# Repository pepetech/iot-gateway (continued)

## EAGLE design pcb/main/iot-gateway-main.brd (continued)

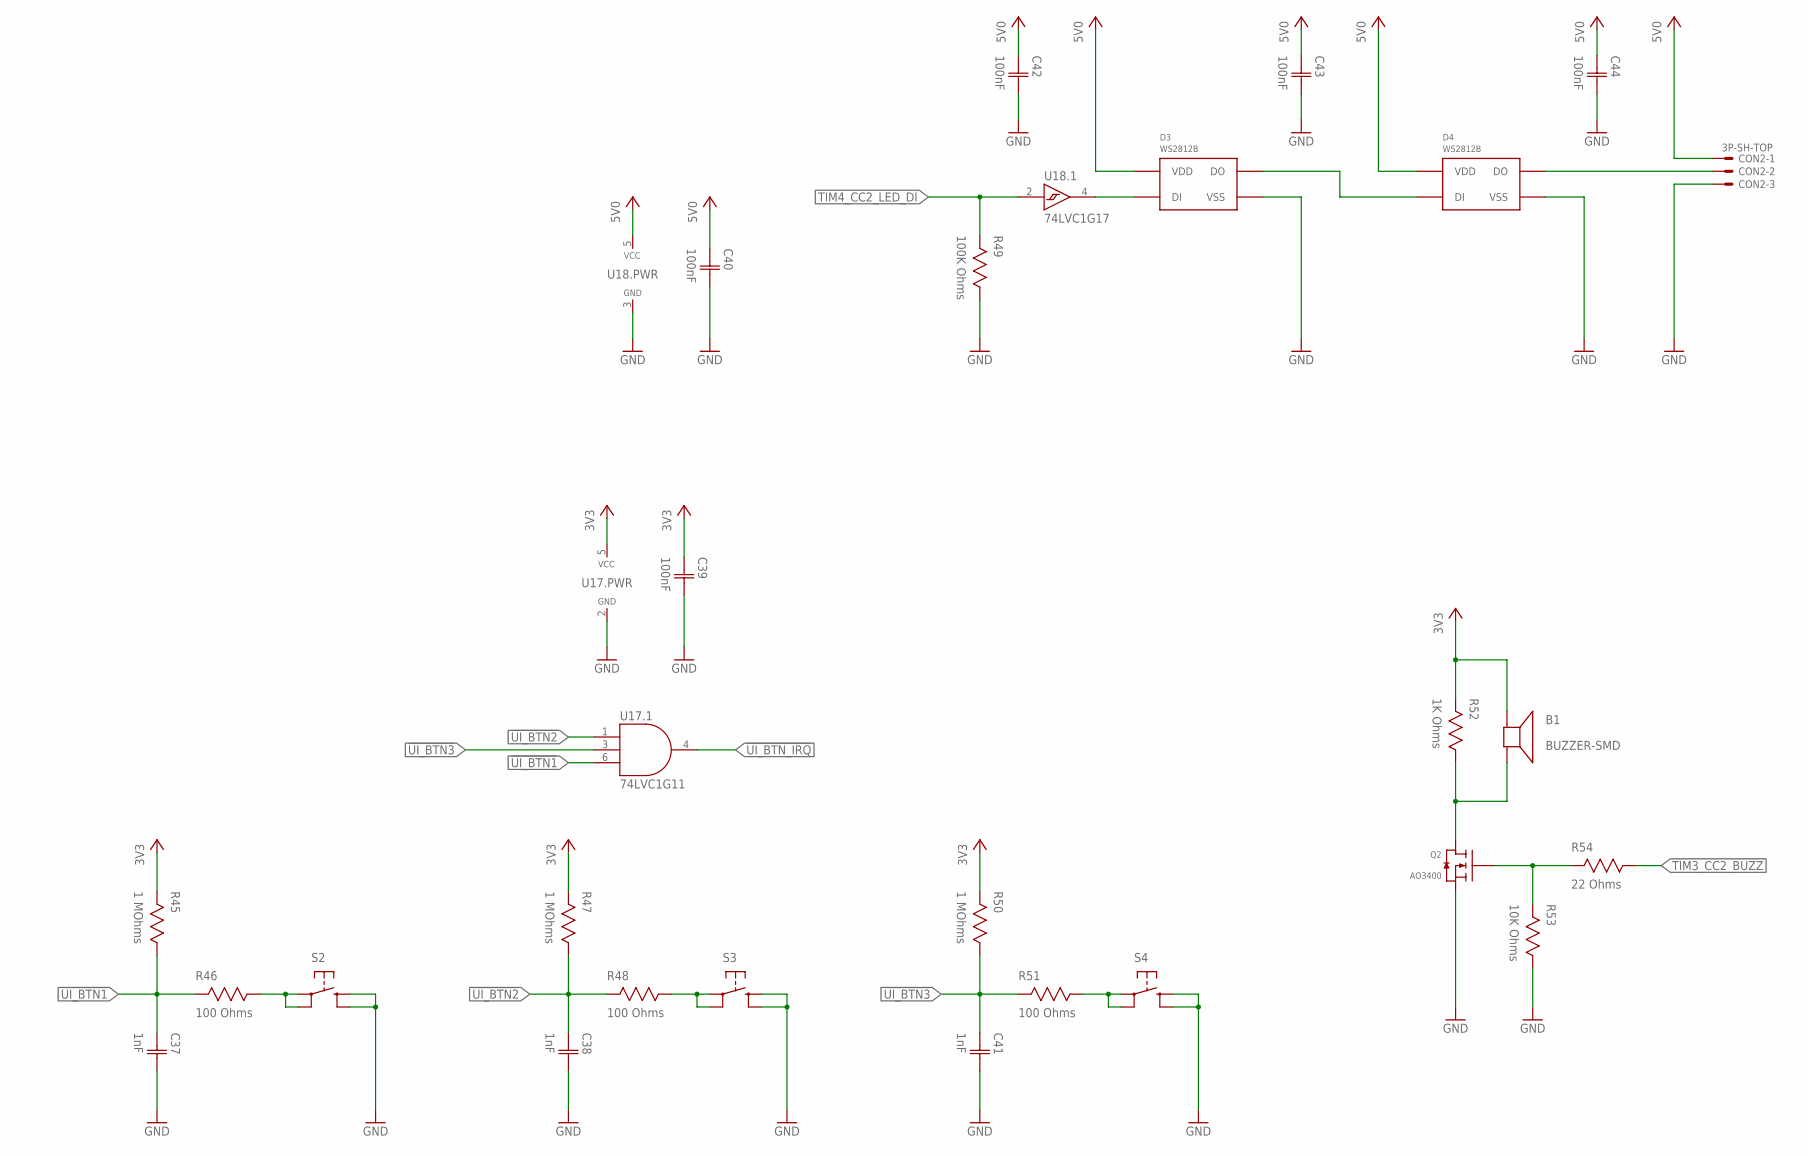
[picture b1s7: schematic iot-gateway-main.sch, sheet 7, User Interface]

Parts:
B1: BUZZER-SMD; SMD
C37, C38, C41: 1nF; CAP0603
C39, C40, C42, C43, C44: 100nF; CAP0603
CON2: 3P-SH-TOP; SH-03-TOP
D3, D4: WS2812B; WS2812B-SMD5050
Q2: AO3400; SOT23
R45, R47, R50: 1 MOhms; RES0603
R46, R48, R51: 100 Ohms; RES0603
R49: 100K Ohms; RES0603
R52: 1K Ohms; RES0603
R53: 10K Ohms; RES0603
R54: 22 Ohms; RES0603
S2, S3, S4: TAC_SWITCHSMD_4.5X4.5; TAC_SW_SMD_4.5X4.5
U17: 74LVC1G11; SC70-6
U18: 74LVC1G17; SC70-5

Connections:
3V3: B1.1 (+), C39.1 (C1), R45.2, R47.2, R50.2, R52.2, U17.5 (VCC); also elsewhere on the board
5V0: C40.1 (C1), C42.1 (C1), C43.1 (C1), C44.1 (C1), CON2.1, D3.1 (VDD), D4.1 (VDD), U18.5 (VCC); also elsewhere on the board
!UI_BTN1: C37.1 (C1), R45.1, R46.2, U17.6 (C); also elsewhere on the board
!UI_BTN2: C38.1 (C1), R47.1, R48.2, U17.1 (A); also elsewhere on the board
!UI_BTN3: C41.1 (C1), R50.1, R51.2, U17.3 (B); also elsewhere on the board
!UI_BTN_IRQ: U17.4 (Y); also elsewhere on the board
BUZZ_DRV: B1.2 (-), Q2.3 (D), R52.1
EXT_LED_DI: CON2.2, D4.2 (DO)
GND: C37.2 (C2), C38.2 (C2), C39.2 (C2), C40.2 (C2), C41.2 (C2), C42.2 (C2), C43.2 (C2), C44.2 (C2), CON2.3, D3.3 (VSS), D4.3 (VSS), Q2.2 (S), R49.1, R53.1, S2.3, S2.4, S3.3, S3.4, S4.3, S4.4, U17.2 (GND), U18.3 (GND); also elsewhere on the board
LED1_DI: D3.4 (DI), U18.4 (Y)
LED2_DI: D3.2 (DO), D4.4 (DI)
unnamed: Q2.1 (G), R53.2, R54.2
unnamed: R46.1, S2.1, S2.2
unnamed: R51.1, S4.1, S4.2
unnamed: R48.1, S3.1, S3.2
TIM3_CC2_BUZZ: R54.1; also elsewhere on the board
TIM4_CC2_LED_DI: R49.2, U18.2 (A); also elsewhere on the board

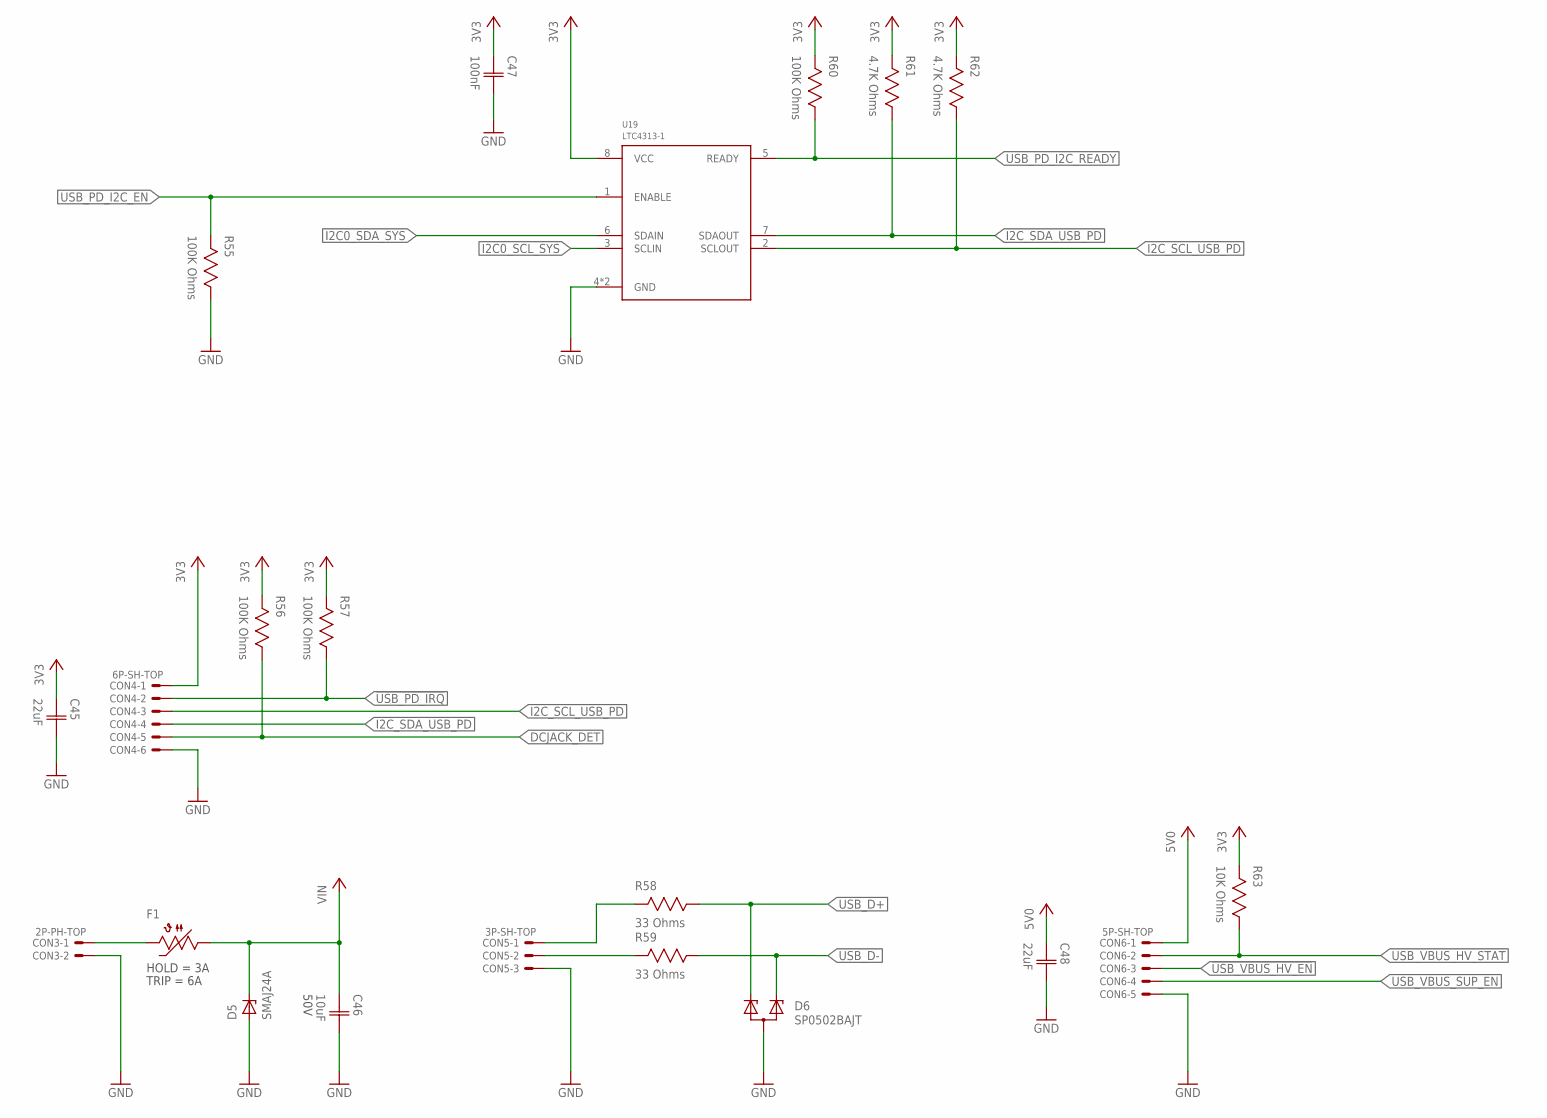
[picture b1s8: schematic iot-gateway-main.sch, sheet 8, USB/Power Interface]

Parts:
C45, C48: 22uF; CAP1206
C46: 10uF; CAP1206; VOLTAGE 50V
C47: 100nF; CAP0603
CON3: 2P-PH-TOP; PH-02-TOP
CON4: 6P-SH-TOP; SH-06-TOP
CON5: 3P-SH-TOP; SH-03-TOP
CON6: 5P-SH-TOP; SH-05-TOP
D5: SMAJ24A; DO214AC
D6: SP0502BAJT; SC70-3
F1: 2.6A Hold; 1206
R55, R56, R57, R60: 100K Ohms; RES0603
R58, R59: 33 Ohms; RES0603
R61, R62: 4.7K Ohms; RES0603
R63: 10K Ohms; RES0603
U19: LTC4313-1; DFN8

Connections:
3V3: C45.1 (C1), C47.1 (C1), CON4.1, R56.2, R57.2, R60.2, R61.2, R62.2, R63.2, U19.8 (VCC); also elsewhere on the board
5V0: C48.1 (C1), CON6.1; also elsewhere on the board
!USB_PD_IRQ: CON4.2, R57.1; also elsewhere on the board
!USB_VBUS_HV_EN: CON6.3; also elsewhere on the board
DCJACK_DET: CON4.5, R56.1; also elsewhere on the board
GND: C45.2 (C2), C46.2 (C2), C47.2 (C2), C48.2 (C2), CON3.2, CON4.6, CON5.3, CON6.5, D5.A, D6.3 (A), R55.1, U19.4 (GND), U19.9 (GND); also elsewhere on the board
I2C0_SCL_SYS: U19.3 (SCLIN); also elsewhere on the board
I2C0_SDA_SYS: U19.6 (SDAIN); also elsewhere on the board
I2C_SCL_USB_PD: CON4.3, R62.1, U19.2 (SCLOUT)
I2C_SDA_USB_PD: CON4.4, R61.1, U19.7 (SDAOUT)
unnamed: CON5.2, R59.2
unnamed: CON5.1, R58.2
USB_D+: D6.1 (C1), R58.1; also elsewhere on the board
USB_D-: D6.2 (C2), R59.1; also elsewhere on the board
USB_PD_I2C_EN: R55.2, U19.1 (ENABLE); also elsewhere on the board
USB_PD_I2C_READY: R60.1, U19.5 (READY); also elsewhere on the board
USB_VBUS_HV_STAT: CON6.2, R63.1; also elsewhere on the board
USB_VBUS_SUP_EN: CON6.4; also elsewhere on the board
VIN: C46.1 (C1), D5.C, F1.1; also elsewhere on the board
VIN_UNFUSED: CON3.1, F1.2

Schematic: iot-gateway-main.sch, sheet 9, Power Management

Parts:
C49, C55, C62, C69, C70, C71, C73, C75, C76: 100nF; CAP0603
C50: 4.7uF; CAP0603; VOLTAGE 35V
C51, C72: 4.7uF; CAP0603
C52, C54: 1uF; CAP0603; VOLTAGE 50V
C53, C59, C60, C61, C64, C65, C74: 470pF; CAP0603
C56: 1uF; CAP0603
C57, C66, C78: 100uF; CAP1206
C58: 10nF; CAP0603
C63: 10pF; CAP0603
C67, C77: 10uF; CAP0603
C68, C79: 22uF; CAP1206
CON7: 2P-PH-TOP; PH-02-TOP
D7: LED1206-REV; 1206_REV
D8: RED; 1206_REV
L3: 470nH; IND3225
L4: 4.7uH; IND0606
L5: 1uH; IND0805
L6: 2.2uH; IND0505
Q3: AO3400; SOT23
Q4: FS8205; SOT23-6
R64: 147K Ohms; RES0603
R65: 21K Ohms; RES0603
R66, R67, R68, R72, R73, R74, R75, R76, R77, R86, R87, R88, R89, R91: 100K Ohms; RES0603
R69: 357K Ohms; RES0603
R70: 61.9K Ohms; RES0603
R71: 41.2K Ohms; RES0603
R78: 1M Ohms; RES0603
R79: 232K Ohms; RES0603
R80: 309K Ohms; RES0603
R81: 71.5K Ohms; RES0603
R82: 510 Ohms; RES0603
R83: 178K Ohms; RES0603
R84: 57.6K Ohms; RES0603
R85: 330 Ohms; RES0603
R90, R95: 2K Ohms; RES0603
R92: 25m Ohms; RES1206
R93: 10m Ohms; RES1206
R94: 100 Ohms; RES0603
R96: 1.5M Ohms; RES0603
R97: 274K Ohms; RES0603
U20: LT8640S; QFN24_CORNER
U21: MIC23159; VQFN20
U22: 74LVC1G04; SC70-5
U23: LTC2942; DFN6
U24: LTC4040; QFN24_ASYM
U25: FS312F-G; SOT23-6

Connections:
3V3: C67.1 (C1), C69.1 (C1), C73.1 (C1), L5.2, R72.2, R73.2, R80.2, R86.2, R87.2, R88.2, R89.2, R91.2, U21.10 (SNS), U22.5 (VCC); also elsewhere on the board
3V3_FB: R80.1, R81.2, U21.11 (FB)
3V3_SS: C64.1 (C1), U21.13 (SS)
3V3_SW: L5.1, U21.4 (SW)
4V2: C55.1 (C1), C57.1 (C1), L3.1, R67.2, R69.2, U21.17 (SNS); also elsewhere on the board
4V2_EN: R66.2, U21.18 (EN); also elsewhere on the board
4V2_FB: R69.1, R70.2, U21.16 (FB)
4V2_PGOOD: R73.1, U21.15 (PG); also elsewhere on the board
4V2_SS: C60.1 (C1), U21.14 (SS)
4V2_SW: L3.2, U21.3 (SW)
4V2_VSENSE: C59.1 (C1), R67.1, R68.2; also elsewhere on the board
5V0: C49.1 (C1), C51.1 (C1), C71.1 (C1), C72.1 (C1), C78.1 (C1), C79.1 (C1), Q3.3 (D), R74.2, R96.2, U21.1 (VIN), U21.6 (VIN), U21.7 (AVIN), U21.9 (EN), U21.20 (AVIN), U24.1 (VSYS), U24.12 (F2), U24.13 (F1), U24.14 (F0), U24.24 (VSYS); also elsewhere on the board
5V0_BACKUP: R85.2, U22.4 (Y)
5V0_FB: R96.1, R97.2, U24.10 (RSTFB), U24.18 (BSTFB)
5V0_GATE: Q3.1 (G), U24.15 (IGATE)
5V0_NBU: Q3.2 (S), R93.1, U24.7 (CLN)
5V0_NBU_ISENSE: C74.1 (C1), U24.3 (CLPROG); also elsewhere on the board
5V0_NBU_NSENS: C63.1 (C1), C66.1 (C1), C68.1 (C1), C70.1 (C1), L4.2, R78.2, R82.2, R83.2, R93.2, U20.1 (BIAS), U24.6 (VIN), U24.16 (OVSNS)
5V0_NBU_NSENS_BST: C62.2 (C2), U20.7 (BST)
5V0_NBU_NSENS_FB: C63.2 (C2), R78.1, R79.2, U20.24 (FB)
5V0_NBU_NSENS_INTVCC: C56.1 (C1), U20.2 (INTVCC), U20.20 (SYNC/MODE)
5V0_NBU_NSENS_PGOOD: R72.1, U20.23 (PG); also elsewhere on the board
5V0_NBU_NSENS_RT: R71.2, U20.18 (RT)
5V0_NBU_NSENS_SS: C58.1 (C1), U20.21 (TR/SS)
5V0_NBU_NSENS_SW: C62.1 (C1), L4.1, U20.8 (SW), U20.9 (SW), U20.10 (SW), U20.11 (SW), U20.12 (SW)
5V0_VSENSE: C61.1 (C1), R74.1, R75.2; also elsewhere on the board
!5V0_BACKUP: R87.1, U22.2 (A), U24.20 (!PFO); also elsewhere on the board
!BAT_CHRG: R89.1, U24.8 (!CHRG); also elsewhere on the board
!BAT_CHRG_EN: R91.1, U24.4 (CHGOFF); also elsewhere on the board
!BAT_FAULT: R88.1, U24.9 (!FAULT); also elsewhere on the board
!FUEL_GAUGE_IRQ: R86.1, U23.5 (!AL!/CC); also elsewhere on the board
BAT_CHRG_PROG: R90.2, U24.2 (PROG)
BAT_OC: Q4.6 (G1), U25.3 (OC)
BAT_OD: Q4.4 (G2), U25.1 (OD)
BAT_PROT_CS: R95.2, U25.2 (CS)
BAT_PROT_VCC: R94.1, U25.5 (VCC)
GBAT: C75.2 (C2), CON7.2, Q4.3 (S2), U25.6 (GND)
GND: C49.2 (C2), C50.2 (C2), C51.2 (C2), C52.2 (C2), C53.2 (C2), C54.2 (C2), C55.2 (C2), C56.2 (C2), C57.2 (C2), C58.2 (C2), C59.2 (C2), C60.2 (C2), C61.2 (C2), C64.2 (C2), C65.2 (C2), C66.2 (C2), C67.2 (C2), C68.2 (C2), C69.2 (C2), C70.2 (C2), C71.2 (C2), C72.2 (C2), C73.2 (C2), C74.2 (C2), C76.2 (C2), C77.2 (C2), C78.2 (C2), C79.2 (C2), D7.C, D8.C, Q4.1 (S1), R65.1, R66.1, R68.1, R70.1, R71.1, R75.1, R77.1, R79.1, R81.1, R84.1, R90.1, R95.1, R97.1, U20.3 (GND), U20.16 (GND), U20.22 (GND), U20.25 (GND), U20.26 (GND), U20.27 (GND), U20.28 (GND), U20.29 (GND), U20.30 (GND), U20.31 (GND), U20.32 (GND), U21.2 (PGND), U21.5 (PGND), U21.8 (AGND), U21.19 (AGND), U21.21 (PGND), U22.3 (GND), U23.2 (GND), U24.5 (BSTOFF), U24.17 (NTC), U24.25 (GND); also elsewhere on the board
I2C0_SCL_SYS: U23.3 (SCL); also elsewhere on the board
I2C0_SDA_SYS: U23.4 (SDA); also elsewhere on the board
unnamed: D7.A, R82.1
unnamed: D8.A, R85.1
PF_THRESH: R83.1, R84.2, U24.19 (PFI)
VBAT: C75.1 (C1), C76.1 (C1), C77.1 (C1), L6.2, R76.2, R92.2, R94.2, U23.1 (VDD/SENSE+), U24.23 (BAT)
VBAT_NSENS: CON7.1, R92.1, U23.6 (VBAT/SENSE-)
VBAT_SW: L6.1, U24.21 (SW), U24.22 (SW)
VBAT_VSENSE: C65.1 (C1), R76.1, R77.2; also elsewhere on the board
VIN: C50.1 (C1), C52.1 (C1), C54.1 (C1), R64.2, U20.5 (VIN), U20.6 (VIN), U20.13 (VIN), U20.14 (VIN), U20.17 (EN/UV); also elsewhere on the board
VIN_VSENSE: C53.1 (C1), R64.1, R65.2; also elsewhere on the board

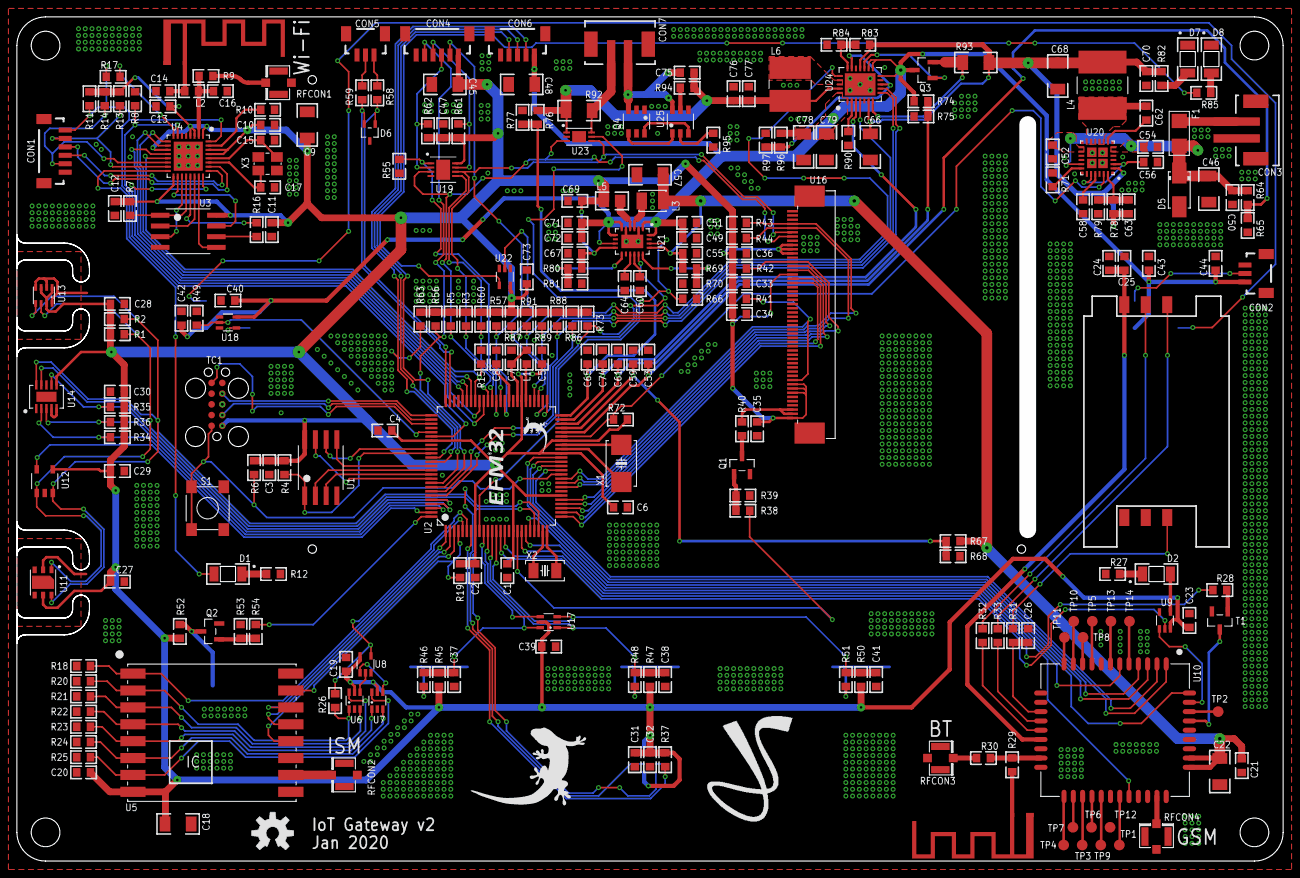
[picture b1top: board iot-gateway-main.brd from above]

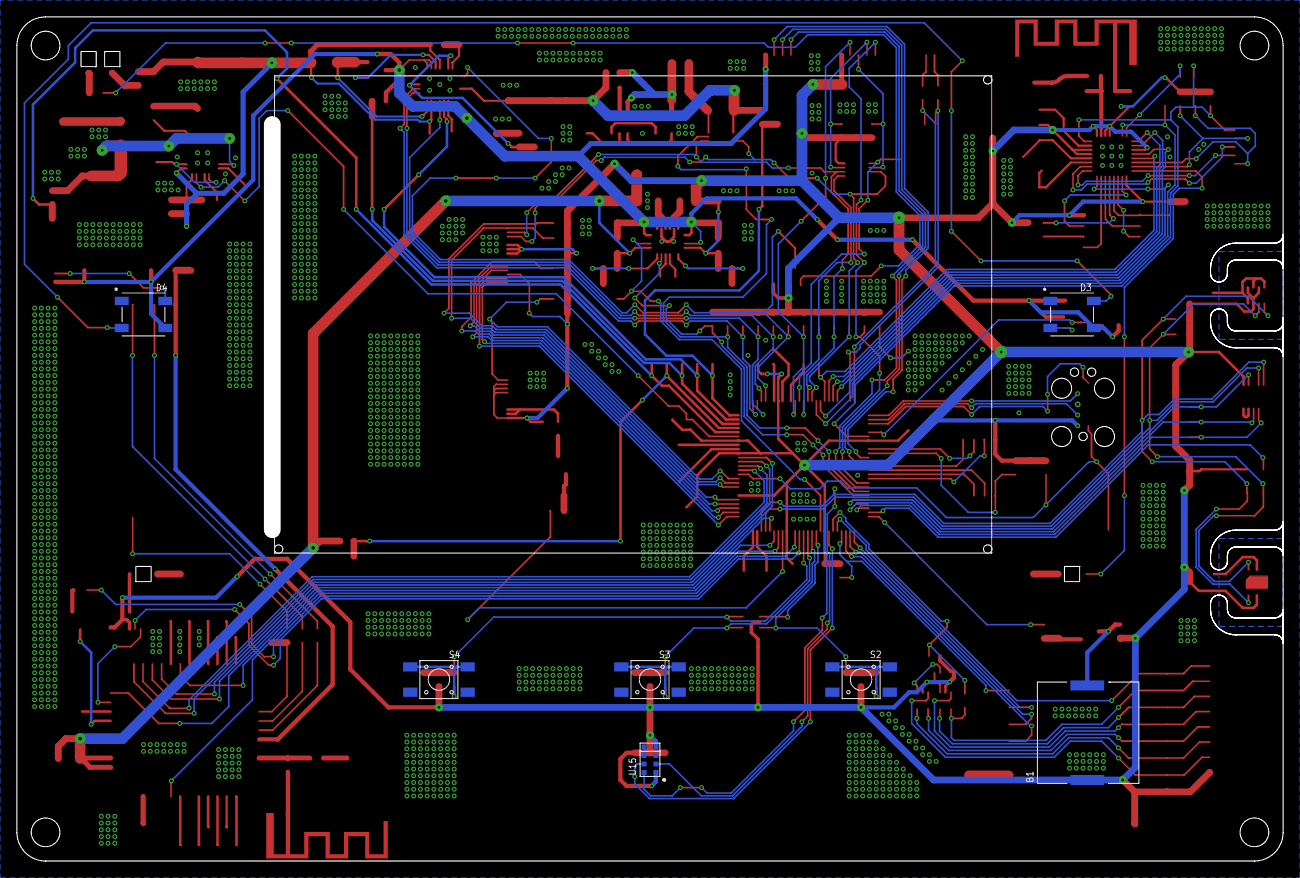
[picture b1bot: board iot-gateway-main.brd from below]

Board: 2 copper layers, 150.0 x 100.0 mm, 261 parts (8 on the bottom side), 195 nets.

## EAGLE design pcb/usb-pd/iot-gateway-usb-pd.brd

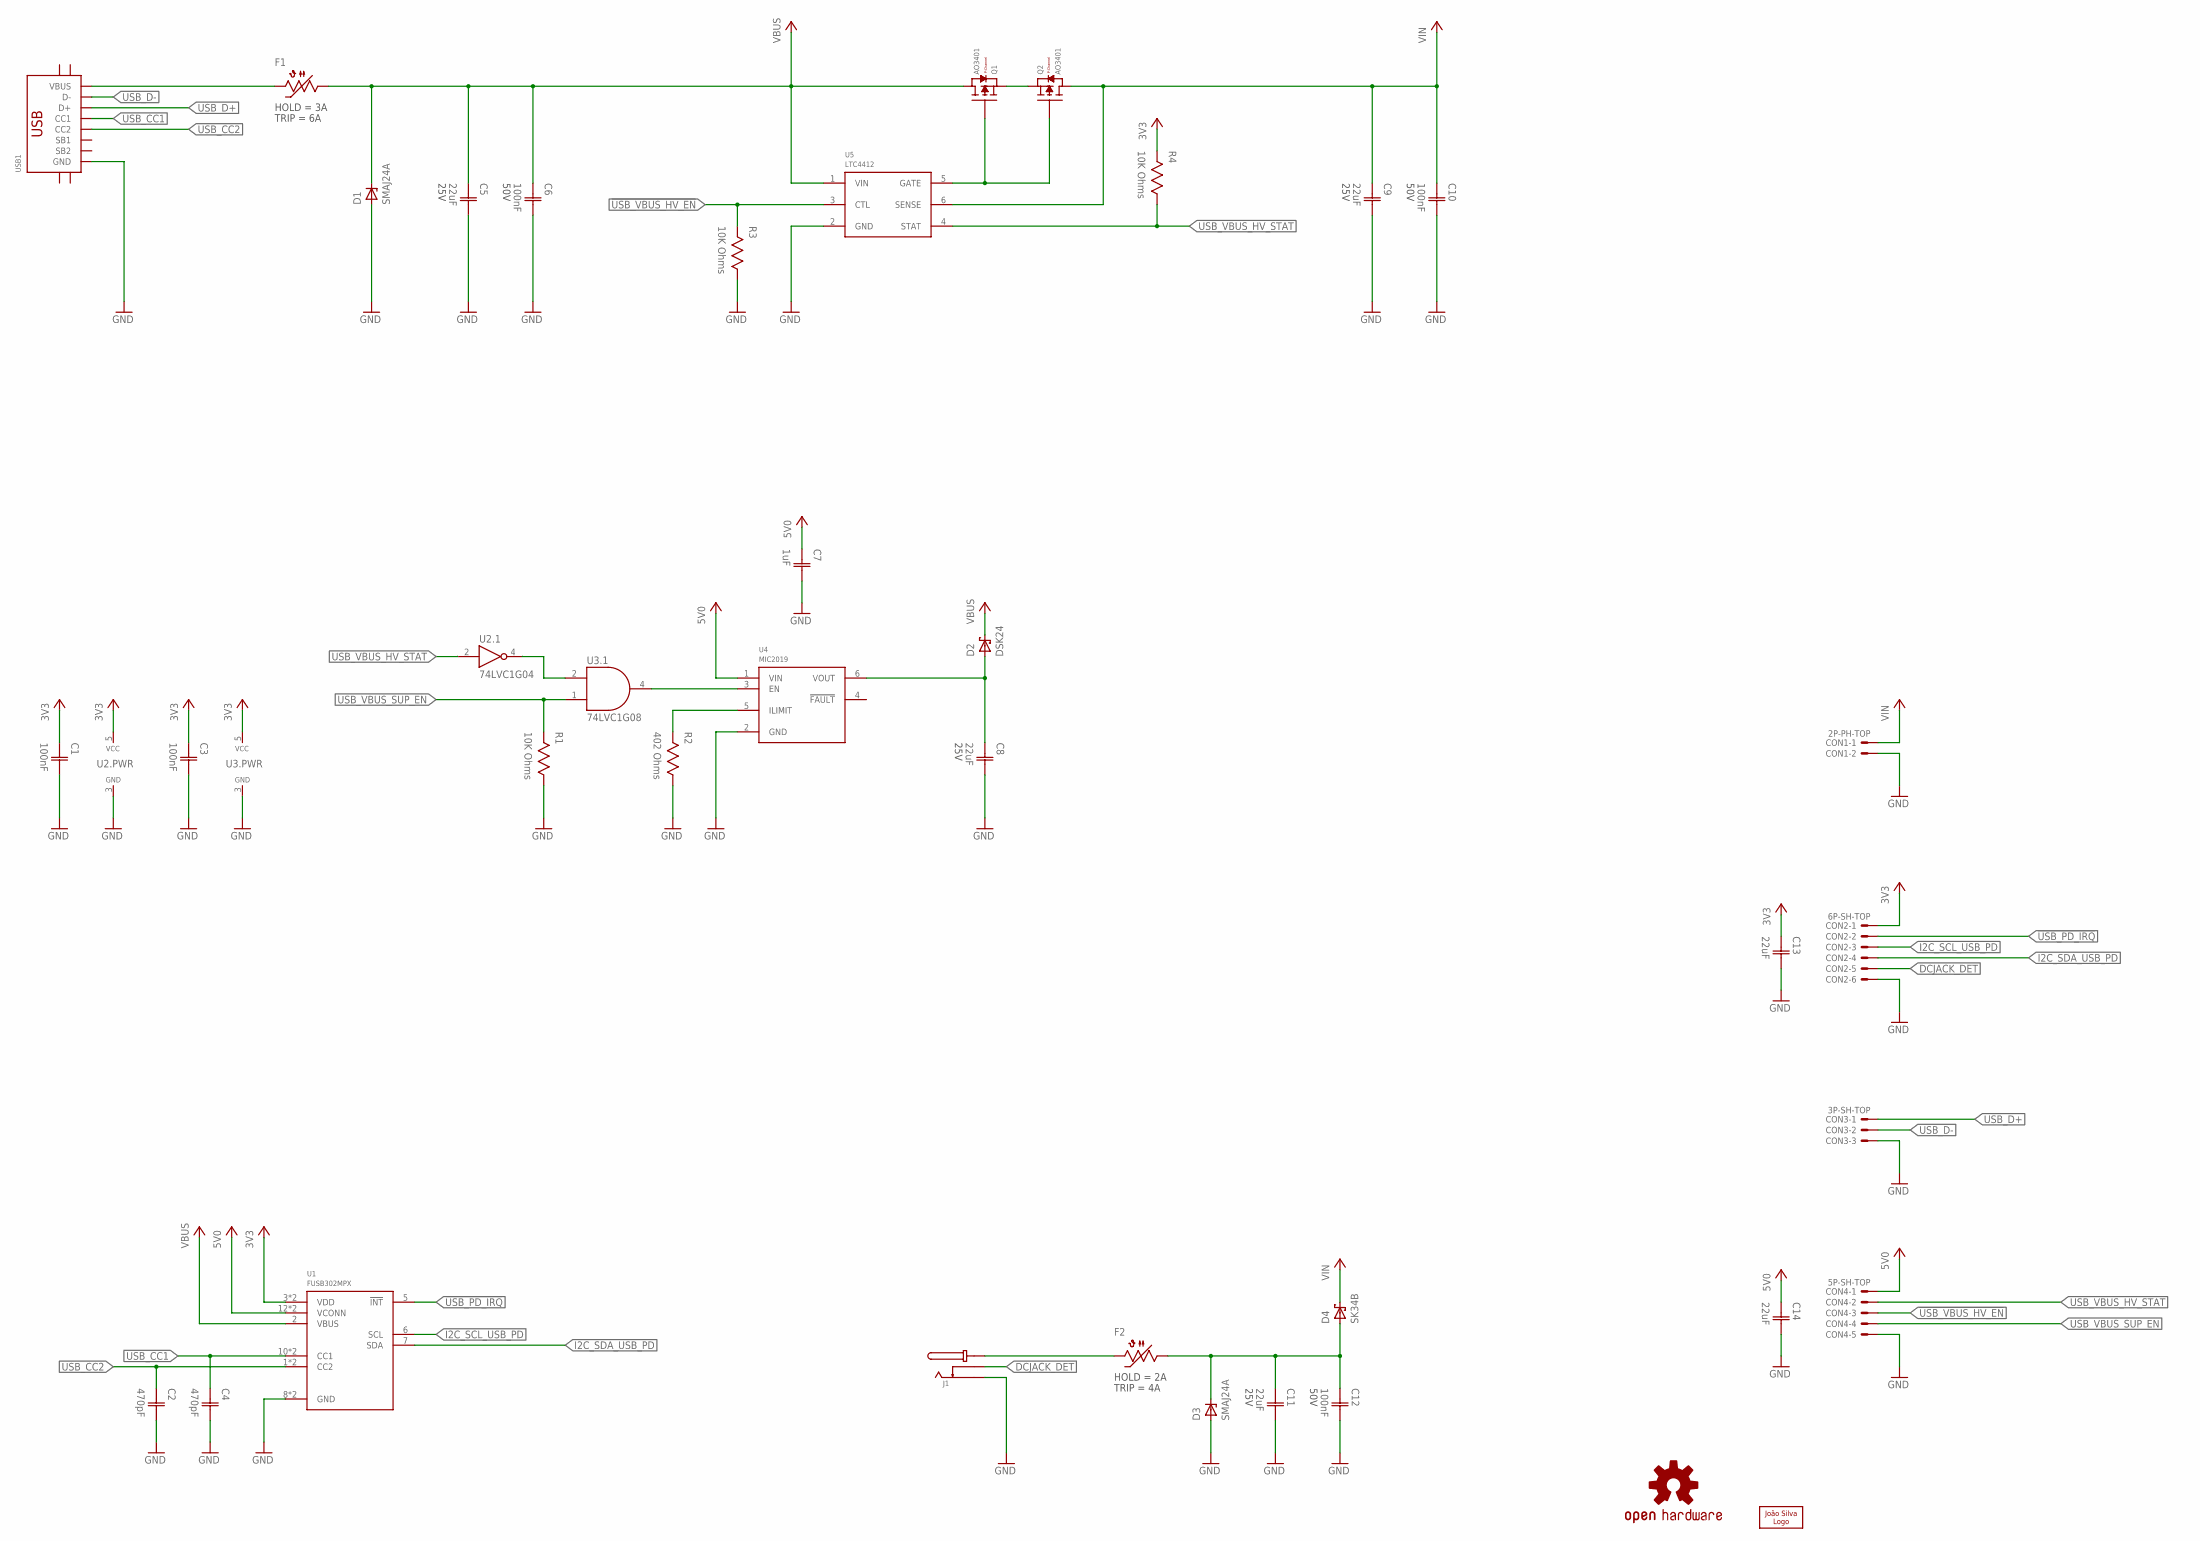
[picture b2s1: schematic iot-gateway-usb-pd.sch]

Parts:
C1, C3: 100nF; CAP0603
C2, C4: 470pF; CAP0603
C5, C8, C9, C11: 22uF; CAP1206; VOLTAGE 25V
C6, C10, C12: 100nF; CAP0603; VOLTAGE 50V
C7: 1uF; CAP0603
C13, C14: 22uF; CAP1206
CON1: 2P-PH-TOP; PH-02-TOP
CON2: 6P-SH-TOP; SH-06-TOP
CON3: 3P-SH-TOP; SH-03-TOP
CON4: 5P-SH-TOP; SH-05-TOP
D1, D3: SMAJ24A; DO214AC
D2: DSK24; SOD-123F
D4: SK34B; DO214AA
F1, F2: PTC1206; 1206
J1: DCJACK; DC-050
LOGO1: OSHW-LOGOS; OSHW-LOGO-S
LOGO2: JS-5MM; JS_5MM
Q1, Q2: AO3401; SOT23
R1, R3, R4: 10K Ohms; RES0603
R2: 402 Ohms; RES0603
U1: FUSB302MPX; QFN14
U2: 74LVC1G04; SC70-5
U3: 74LVC1G08; SC70-5
U4: MIC2019; SOT23-6
U5: LTC4412; SOT23-6
USB1: USB-C-16P-SMD-FLAT-SIDE-TYPE-2

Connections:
3V3: C1.1 (C1), C3.1 (C1), C13.1 (C1), CON2.1, R4.2, U1.3 (VDD), U1.4 (VDD), U2.5 (VCC), U3.5 (VCC)
5V0: C7.1 (C1), C14.1 (C1), CON4.1, U1.12 (VCONN), U1.13 (VCONN), U4.1 (VIN)
!USB_PD_IRQ: CON2.2, U1.5 (!INT)
!USB_VBUS_HV_EN: CON4.3, R3.2, U5.3 (CTL)
!USB_VBUS_HV_STAT: U2.4 (Y), U3.2 (A)
DCJACK_DET: CON2.5, J1.DT
GND: C1.2 (C2), C2.2 (C2), C3.2 (C2), C4.2 (C2), C5.2 (C2), C6.2 (C2), C7.2 (C2), C8.2 (C2), C9.2 (C2), C10.2 (C2), C11.2 (C2), C12.2 (C2), C13.2 (C2), C14.2 (C2), CON1.2, CON2.6, CON3.3, CON4.5, D1.A, D3.A, J1.O, R1.1, R2.1, R3.1, U1.8 (GND), U1.9 (GND), U2.3 (GND), U3.3 (GND), U4.2 (GND), U5.2 (GND), USB1.A1/B12 (GND), USB1.B1/A12 (GND)
I2C_SCL_USB_PD: CON2.3, U1.6 (SCL)
I2C_SDA_USB_PD: CON2.4, U1.7 (SDA)
unnamed: Q1.2 (S), Q2.2 (S)
unnamed: Q1.1 (G), Q2.1 (G), U5.5 (GATE)
unnamed: R2.2, U4.5 (ILIMIT)
USB_CC1: C4.1 (C1), U1.10 (CC1), U1.11 (CC1), USB1.A5 (CC1)
USB_CC2: C2.1 (C1), U1.1 (CC2), U1.14 (CC2), USB1.B5 (CC2)
USB_D+: CON3.1, USB1.A6 (D+), USB1.B6 (D+)
USB_D-: CON3.2, USB1.A7 (D-), USB1.B7 (D-)
USB_VBUS_HV_STAT: CON4.2, R4.1, U2.2 (A), U5.4 (STAT)
USB_VBUS_SUP_EN: CON4.4, R1.2, U3.1 (B)
USB_VBUS_SUP_EN_Q: U3.4 (Y), U4.3 (EN)
VBUS: C5.1 (C1), C6.1 (C1), D1.C, D2.C, F1.1, Q1.3 (D), U1.2 (VBUS), U5.1 (VIN)
VBUS_SRC: C8.1 (C1), D2.A, U4.6 (VOUT)
VBUS_UNFUSED: F1.2, USB1.A4/B9 (VBUS), USB1.B4/A9 (VBUS)
VIN: C9.1 (C1), C10.1 (C1), CON1.1, D4.C, Q2.3 (D), U5.6 (SENSE)
VJACK: C11.1 (C1), C12.1 (C1), D3.C, D4.A, F2.1
VJACK_UNFUSED: F2.2, J1.C, J1.C' (C)

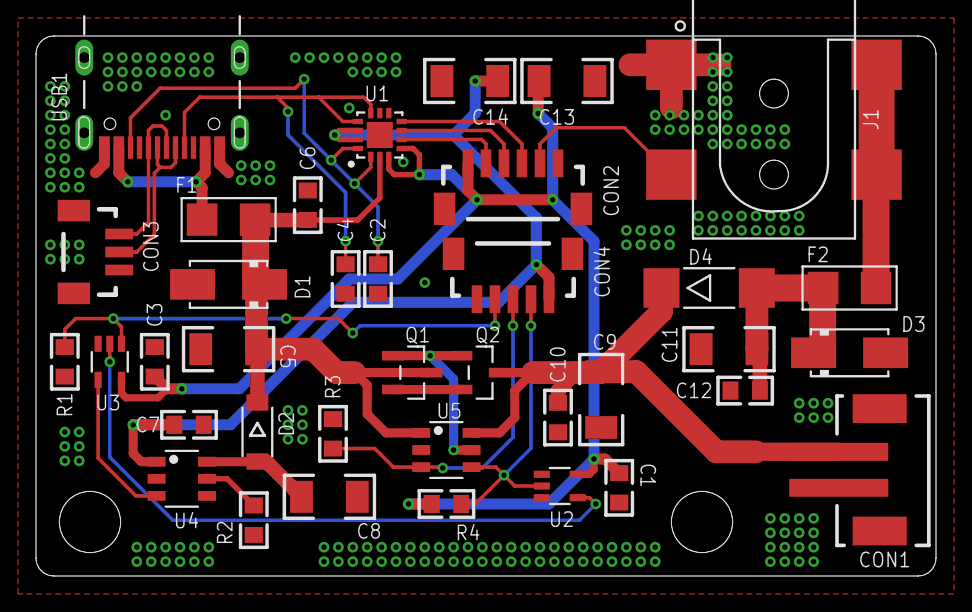
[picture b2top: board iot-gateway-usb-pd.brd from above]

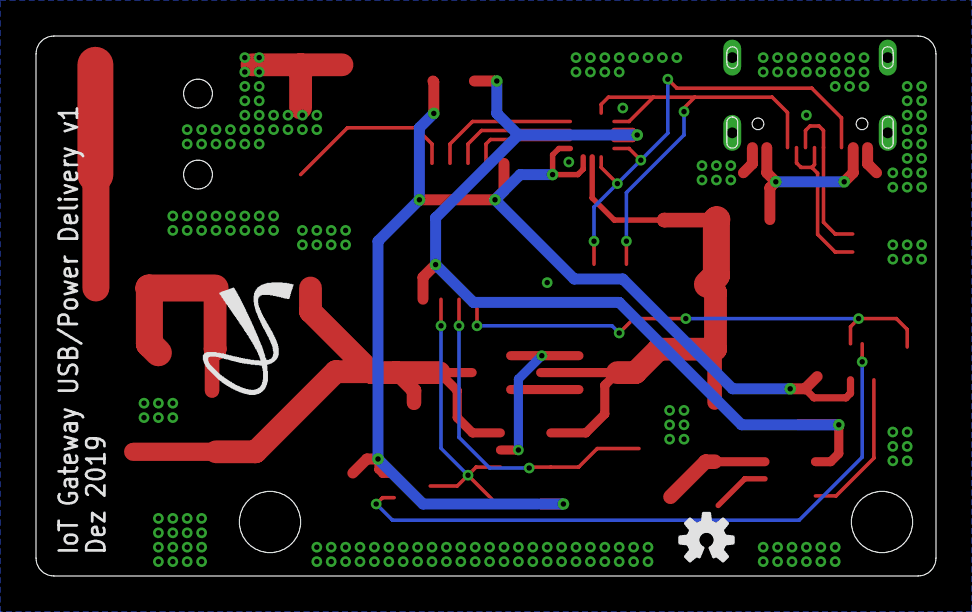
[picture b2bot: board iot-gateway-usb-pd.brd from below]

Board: 2 copper layers, 50.0 x 30.0 mm, 39 parts (2 on the bottom side), 25 nets.

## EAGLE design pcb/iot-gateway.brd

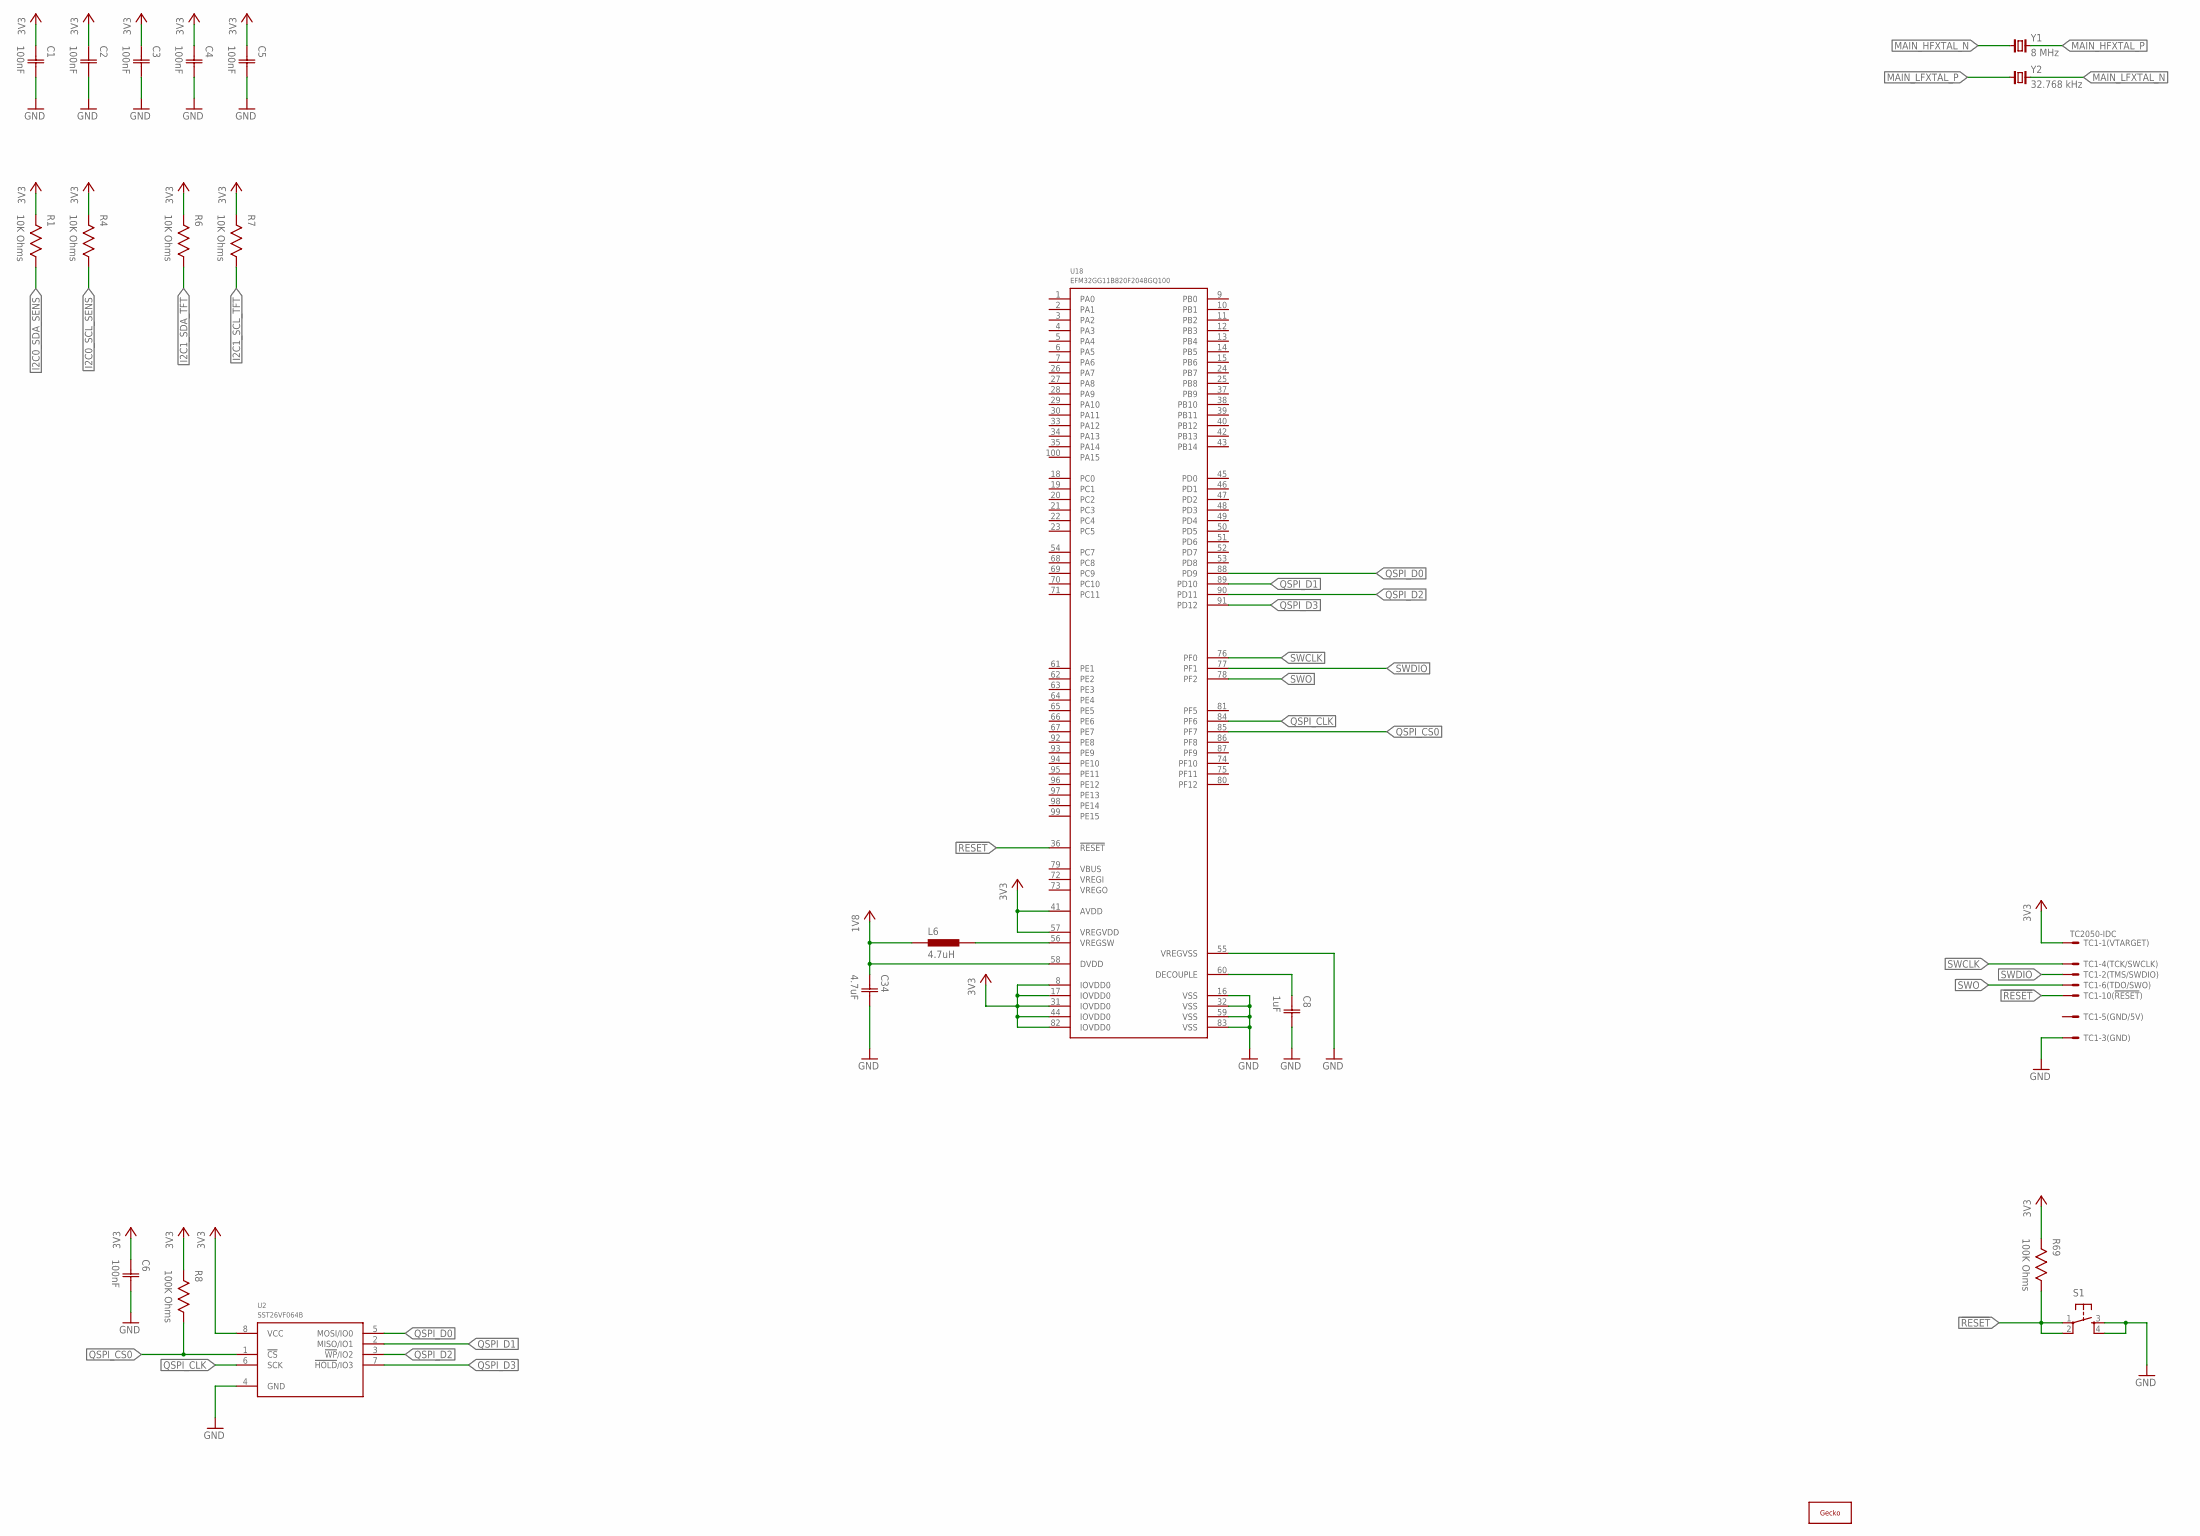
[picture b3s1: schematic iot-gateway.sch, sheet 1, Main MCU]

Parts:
C1, C2, C3, C4, C5, C6: 100nF; CAP0603
C8: 1uF; CAP0603
C34: 4.7uF; CAP0603
L6: 4.7uH; IND0603
R1, R4, R6, R7: 10K Ohms; RES0603
R8, R69: 100K Ohms; RES0603
S1: TAC_SWITCHSMD; TAC_SW_SMD_RESET
TC1: TC2050-IDC
U2: SST26VF064B; WSOIC8
U18: EFM32GG11B820F2048GQ100; QFP100
U$1: GECKO-14MM; GECKO_14MM
Y1: 8 MHz; 2-SMD-5032
Y2: 32.768 kHz; CM200S

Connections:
1V8: C34.1 (C1), L6.1, U18.58 (DVDD)
3V3: C1.1 (C1), C2.1 (C1), C3.1 (C1), C4.1 (C1), C5.1 (C1), C6.1 (C1), R1.2, R4.2, R6.2, R7.2, R8.2, R69.2, TC1.1, U2.8 (VCC), U18.8 (IOVDD0), U18.17 (IOVDD0), U18.31 (IOVDD0), U18.41 (AVDD), U18.44 (IOVDD0), U18.57 (VREGVDD), U18.82 (IOVDD0); also elsewhere on the board
!RESET: R69.1, S1.1, S1.2, TC1.10, U18.36 (!RESET)
GND: C1.2 (C2), C2.2 (C2), C3.2 (C2), C4.2 (C2), C5.2 (C2), C6.2 (C2), C8.2 (C2), C34.2 (C2), S1.3, S1.4, TC1.3, U2.4 (GND), U18.16 (VSS), U18.32 (VSS), U18.55 (VREGVSS), U18.59 (VSS), U18.83 (VSS); also elsewhere on the board
I2C0_SCL_SENS: R4.1; also elsewhere on the board
I2C0_SDA_SENS: R1.1; also elsewhere on the board
I2C1_SCL_TFT: R7.1; also elsewhere on the board
I2C1_SDA_TFT: R6.1; also elsewhere on the board
MAIN_HFXTAL_N: Y1.1
MAIN_HFXTAL_P: Y1.2
MAIN_LFXTAL_N: Y2.4 (2)
MAIN_LFXTAL_P: Y2.1
unnamed: C8.1 (C1), U18.60 (DECOUPLE)
unnamed: L6.2, U18.56 (VREGSW)
QSPI_CLK: U2.6 (SCK), U18.84 (PF6)
QSPI_CS0: R8.1, U2.1 (!CS!), U18.85 (PF7)
QSPI_D0: U2.5 (MOSI/IO0), U18.88 (PD9)
QSPI_D1: U2.2 (MISO/IO1), U18.89 (PD10)
QSPI_D2: U2.3 (!WP!/IO2), U18.90 (PD11)
QSPI_D3: U2.7 (!HOLD!/IO3), U18.91 (PD12)
SWCLK: TC1.4, U18.76 (PF0)
SWDIO: TC1.2, U18.77 (PF1)
SWO: TC1.6, U18.78 (PF2)
